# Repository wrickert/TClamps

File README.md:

#Programming POGO Pin Clamps
These are the PCB files and 3d models for my POGO pin clamp jigs

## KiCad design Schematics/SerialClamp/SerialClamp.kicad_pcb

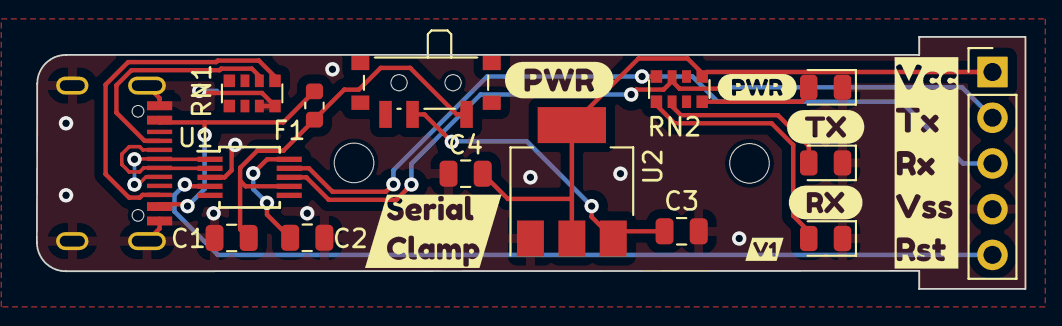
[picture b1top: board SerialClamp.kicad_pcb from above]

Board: 2 copper layers, 54.9 x 14.0 mm, 24 parts (0 on the bottom side), 16 nets.

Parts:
C1, C2: 100nF; C_0805_2012Metric
C3, C4: 10uF; C_0805_2012Metric
D1, D2, D3: LED_Small; LED_0805_2012Metric
F1: Polyfuse_Small; Fuse_0603_1608Metric
H1, H2: MountingHole; MountingHole_2.2mm_M2
J1: USB_C_Receptacle_USB2.0; USB_C_Receptical-Jing
J2: Conn_01x05; PinHeader_1x05_P2.54mm_Vertical
RN1: 5.1k; R_Array_Convex_4x0612
RN2: 330; R_Array_Convex_4x0612
SW1: Power; SW_SPDT_PCM12
U1: CH340E; MSOP-10_3x3mm_P0.5mm
U2: LD1117S12TR_SOT223; SOT-223-3_TabPin2
kibuzzard-65CB8E97: G***; kibuzzard-65CB8E97
kibuzzard-65CB9ADE: G***; kibuzzard-65CB9ADE
kibuzzard-65CB9AFE: G***; kibuzzard-65CB9AFE
kibuzzard-65CB9B2E: G***; kibuzzard-65CB9B2E
kibuzzard-65CB9B05: G***; kibuzzard-65CB9B05
kibuzzard-65CB9C81: G***; kibuzzard-65CB9C81
kibuzzard-65CB9418: G***; kibuzzard-65CB9418

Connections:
D+: J1.A6 (D+), J1.B6 (D+), U1.1 (UD+)
D-: J1.A7 (D-), J1.B7 (D-), U1.2 (UD-)
unnamed: D1.2 (A), RN2.5 (R4.2)
unnamed: D2.2 (A), RN2.6 (R3.2)
unnamed: D3.2 (A), RN2.8 (R1.2)
unnamed: F1.1, J1.A4 (VBUS), J1.A9 (VBUS), J1.B4 (VBUS), J1.B9 (VBUS)
unnamed: J1.A5 (CC1), RN1.6 (R3.2)
unnamed: J1.B5 (CC2), RN1.5 (R4.2)
unnamed: C3.1, SW1.2 (B), U2.3 (VI)
unnamed: C2.1, U1.10 (V3)
RX: J2.3, RN2.4 (R4.1), U1.9 (RXD)
Reset: J2.5, U1.4 (~RTS)
TX: J2.2, RN2.3 (R3.1), U1.8 (TXD)
VCC: C4.1, J2.1, RN2.1 (R1.1), U2.2 (VO)
VSS: C1.2, C2.2, C3.2, C4.2, D1.1 (K), D2.1 (K), D3.1 (K), J1.A1 (GND), J1.A12 (GND), J1.B1 (GND), J1.B12 (GND), J1.S1 (SHIELD), J2.4, RN1.3 (R3.1), RN1.4 (R4.1), U1.3 (GND), U2.1 (GND)
VUSB: C1.1, F1.2, SW1.1 (A), U1.7 (VCC)

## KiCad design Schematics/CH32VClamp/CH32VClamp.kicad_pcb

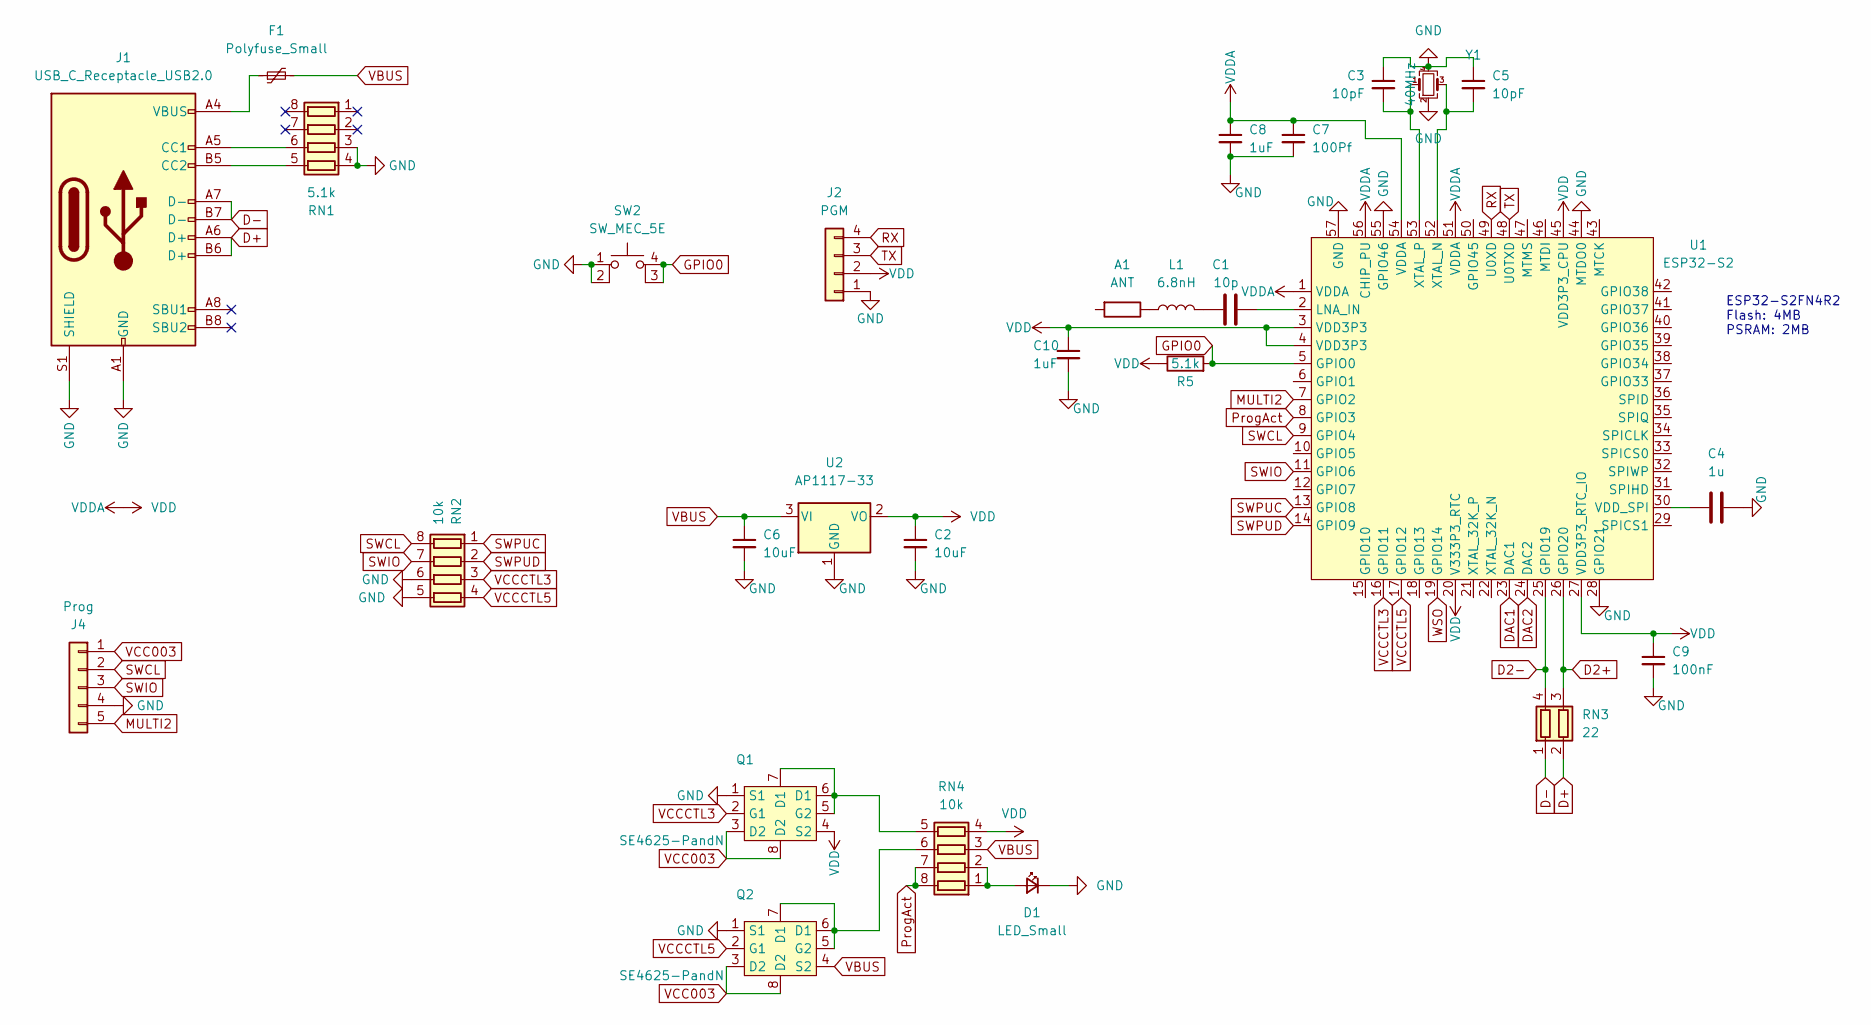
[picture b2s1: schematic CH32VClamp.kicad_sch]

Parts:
A1: ANT; R_1206_3216Metric; LCSC C127629
C1: 10p; C_0805_2012Metric; LCSC C106199
C2, C6: 10uF; C_0805_2012Metric
C3, C5: 10pF; C_0603_1608Metric
C4: 1u; C_0805_2012Metric; LCSC C106254
C7: 100Pf; C_0603_1608Metric
C8, C10: 1uF; C_0603_1608Metric
C9: 100nF; C_0805_2012Metric
D1: LED_Small; LED_0603_1608Metric
F1: Polyfuse_Small; Fuse_0603_1608Metric
J1: USB_C_Receptacle_USB2.0; USB_C_Receptical-Jing
J2: PGM; PinHeader_1x04_P1.00mm_Vertical; LCSC NP
J4: Prog; PinHeader_1x05_P2.54mm_Vertical
L1: 6.8nH; L_0402_1005Metric; LCSC C77110
Q1, Q2: SE4625-PandN; DFN-6-2x2-SplitPad; LCSC C730094
R5: 5.1k; R_0603_1608Metric; LCSC C105872
RN1: 5.1k; R_Array_Convex_4x0612
RN2, RN4: 10k; R_Array_Convex_4x0612
RN3: 22; R_Array_Convex_2x0603
SW2: SW_MEC_5E; TS3315A
U1: ESP32-S2; QFN-56-1EP_7x7mm_P0.4mm_EP3.2x3.2mm; LCSC C2840995
U2: AP1117-33; SOT-23; LCSC C6186
Y1: 40MHz; Crystal_SMD_2016-4Pin_2.0x1.6mm; LCSC C648970

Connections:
D2+: RN3.3 (R2.2), U1.26 (GPIO20)
D2-: RN3.4 (R1.2), U1.25 (GPIO19)
D+: J1.A6 (D+), J1.B6 (D+), RN3.2 (R2.1)
D-: J1.A7 (D-), J1.B7 (D-), RN3.1 (R1.1)
DAC1: U1.23 (DAC1)
DAC2: U1.24 (DAC2)
GND: C2.2, C3.1, C4.2, C5.1, C6.2, C7.2, C8.2, C9.2, C10.2, D1.1 (K), J1.A1 (GND), J1.A12 (GND), J1.B1 (GND), J1.B12 (GND), J1.S1 (SHIELD), J2.1, J4.4, Q1.1 (S1), Q2.1 (S1), RN1.3 (R3.1), RN1.4 (R4.1), RN2.5 (R4.2), RN2.6 (R3.2), SW2.1, SW2.2, U1.28 (GPIO21), U1.44 (MTDO0), U1.55 (GPIO46), U1.57 (GND), U2.1 (GND), Y1.2, Y1.4
GPIO0: R5.2, SW2.3 (K), SW2.4 (A), U1.5 (GPIO0)
MULTI2: J4.5, U1.7 (GPIO2)
unnamed: A1.1, L1.1
unnamed: C1.1, L1.2
unnamed: D1.2 (A), RN4.1 (R1.1), RN4.2 (R2.1)
unnamed: F1.1, J1.A4 (VBUS), J1.A9 (VBUS), J1.B4 (VBUS), J1.B9 (VBUS)
unnamed: J1.A5 (CC1), RN1.6 (R3.2)
unnamed: J1.B5 (CC2), RN1.5 (R4.2)
unnamed: Q1.5 (G2), Q1.6 (D1), Q1.7 (D1), RN4.5 (R4.2)
unnamed: Q2.5 (G2), Q2.6 (D1), Q2.7 (D1), RN4.6 (R3.2)
unnamed: C1.2, U1.2 (LNA_IN)
unnamed: C4.1, U1.30 (VDD_SPI)
unnamed: C5.2, U1.52 (XTAL_N), Y1.3
unnamed: C3.2, U1.53 (XTAL_P), Y1.1
ProgAct: RN4.7 (R2.2), RN4.8 (R1.2), U1.8 (GPIO3)
RX: J2.4, U1.49 (U0XD)
SWCL: J4.2, RN2.8 (R1.2), U1.9 (GPIO4)
SWIO: J4.3, RN2.7 (R2.2), U1.11 (GPIO6)
SWPUC: RN2.1 (R1.1), U1.13 (GPIO8)
SWPUD: RN2.2 (R2.1), U1.14 (GPIO9)
TX: J2.3, U1.48 (U0TXD)
VBUS: C6.1, F1.2, Q2.4 (S2), RN4.3 (R3.1), U2.3 (VI)
VCC003: J4.1, Q1.3 (D2), Q1.8 (D2), Q2.3 (D2), Q2.8 (D2)
VCCCTL3: Q1.2 (G1), RN2.3 (R3.1), U1.16 (GPIO11)
VCCCTL5: Q2.2 (G1), RN2.4 (R4.1), U1.17 (GPIO12)
VDD: C2.1, C7.1, C8.1, C9.1, C10.1, J2.2, Q1.4 (S2), R5.1, RN4.4 (R4.1), U1.1 (VDDA), U1.3 (VDD3P3), U1.4 (VDD3P3), U1.20 (V333P3_RTC), U1.27 (VDD3P3_RTC_IO), U1.45 (VDD3P3_CPU), U1.51 (VDDA), U1.54 (VDDA), U1.56 (CHIP_PU), U2.2 (VO)
WSO: U1.19 (GPIO14)

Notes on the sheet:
ESP32-S2FN4R2 Flash: 4MB PSRAM: 2MB

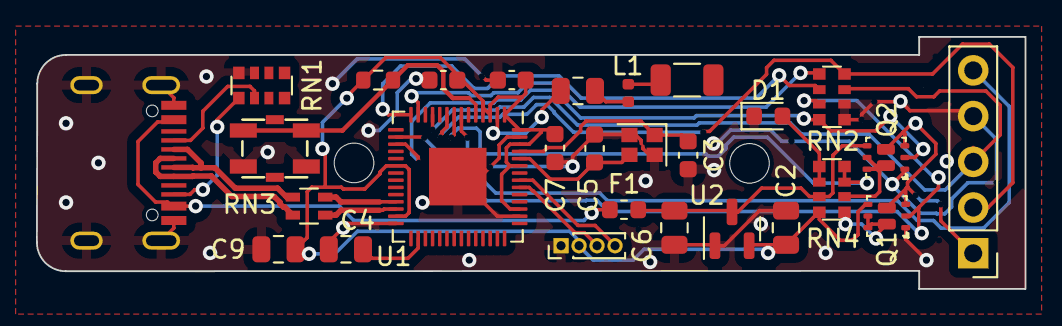
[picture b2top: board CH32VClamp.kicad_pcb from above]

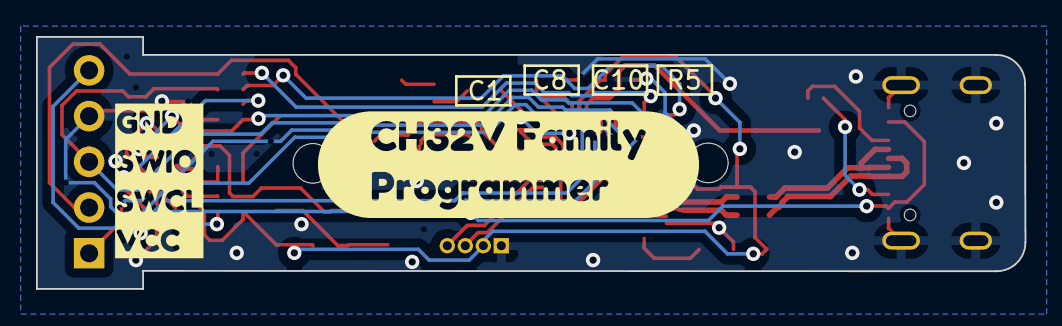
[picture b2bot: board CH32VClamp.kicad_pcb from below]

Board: 2 copper layers, 54.9 x 14.0 mm, 30 parts (2 on the bottom side), 31 nets.

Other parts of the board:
kibuzzard-65DCFED4: G***; kibuzzard-65DCFED4
kibuzzard-65DCFFD3: G***; kibuzzard-65DCFFD3

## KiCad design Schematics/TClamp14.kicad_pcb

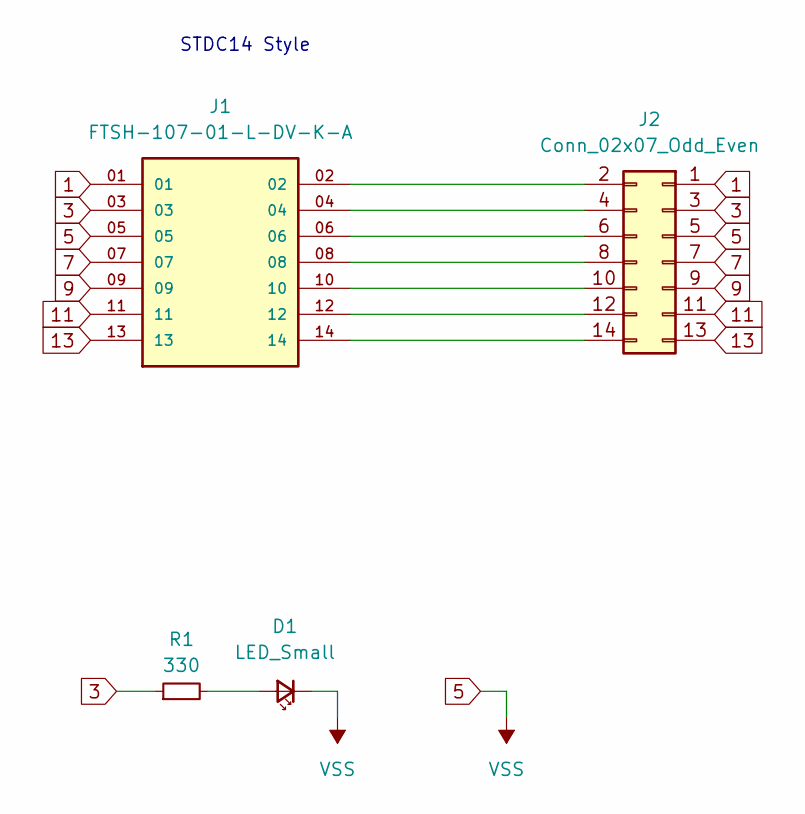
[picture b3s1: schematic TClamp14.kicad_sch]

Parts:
D1: LED_Small; LED_0603_1608Metric
J1: FTSH-107-01-L-DV-K-A; SAMTEC_FTSH-107-01-L-DV-K-A; PARTREV H
J2: Conn_02x07_Odd_Even; PinHeader_2x07_P1.27mm_Vertical
R1: 330; R_0603_1608Metric

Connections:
1: J1.01, J2.1
3: J1.03, J2.3, R1.1
5: D1.1 (K), J1.05, J2.5
7: J1.07, J2.7
9: J1.09, J2.9
11: J1.11, J2.11
13: J1.13, J2.13
unnamed: D1.2 (A), R1.2
unnamed: J1.02, J2.2
unnamed: J1.04, J2.4
unnamed: J1.06, J2.6
unnamed: J1.08, J2.8
unnamed: J1.10, J2.10
unnamed: J1.12, J2.12
unnamed: J1.14, J2.14

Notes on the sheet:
STDC14 Style

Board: 2 copper layers, 4 parts (0 on the bottom side), 15 nets, no tracks yet.

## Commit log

2023-10-27 Started Kicad
2023-10-27 Schematic Finished.
2024-02-09 Started serialClamp
2024-02-22 Added serial and started work on CH32
2024-02-26 Decide on standard and started routing
2024-02-27 Ordered CH32V Clamp V1
2024-02-28 Recieved PCBs and started CAD
